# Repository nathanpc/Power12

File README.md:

# Power12

A compact 6 watts per channel amplifier.

## Schematic

It's a very simple discrete power amplifier with a [CFP output stage](http://en.wikipedia.org/wiki/Sziklai_pair).

## Distortion

*Rev A*

Here's the THD x Frequency plot created using [plot_thd.py](https://gist.github.com/nathanpc/464b65f48d494179be13):

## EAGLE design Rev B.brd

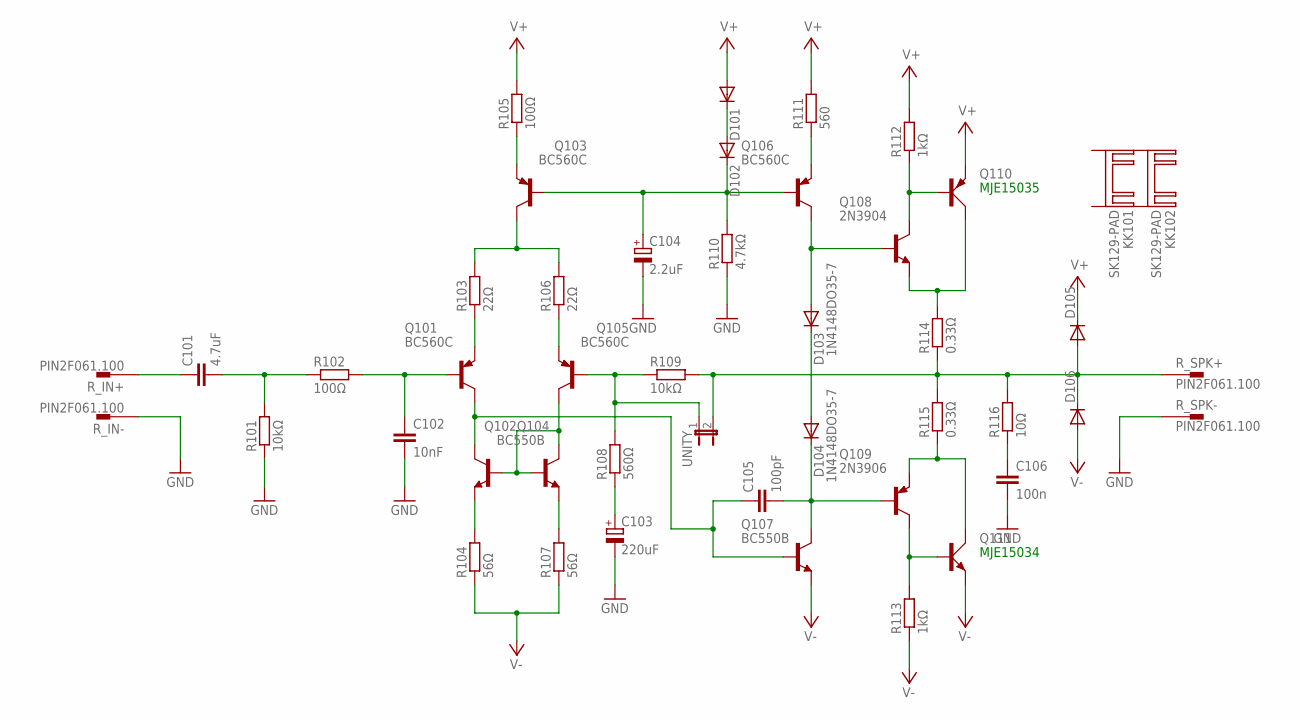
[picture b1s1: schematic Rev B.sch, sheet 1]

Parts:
C101: 4.7uF; C225-113X268
C102: 10nF; C025-025X050
C103: 220uF; E3,5-8
C104: 2.2uF; E2-5
C105: 100pF; C050-050X075
C106: 100n; C075-042X103
D101, D102, D103, D104, D105, D106: 1N4148DO35-7; DO35-7
KK101, KK102: SK129-PAD; SK129
Q101, Q103, Q105, Q106: BC560C; TO92-EBC
Q102, Q104, Q107: BC550B; TO92-EBC
Q108: 2N3904; TO92
Q109: 2N3906; TO92
Q110: TIP42C; TO220AV
Q111: TIP41C; TO220AV
R101, R109: 10kΩ; 0207/10
R102, R105: 100Ω; 0207/10
R103, R106: 22Ω; 0207/10
R104, R107: 56Ω; 0207/10
R108: 560Ω; 0207/10
R110: 4.7kΩ; 0207/10
R111: 560; 0207/10
R112, R113: 1kΩ; 0207/10
R114, R115: 0.33Ω; 0309/12
R116: 10Ω; 0617V
R_IN+: PIN2F061.100; F061.100
R_IN-: PIN2F061.100; F061.100
R_SPK+: PIN2F061.100; F061.100
R_SPK-: PIN2F061.100; F061.100
UNITY: JP1E; JP1

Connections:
GND: C102.2, C103.-, C104.-, C106.2, R101.1, R110.1, R_IN-.A1, R_IN-.A2, R_SPK-.A1, R_SPK-.A2; also elsewhere on the board
unnamed: D103.A, Q106.C, Q108.2 (B)
unnamed: Q105.E, R106.1
unnamed: Q102.B, Q104.B, Q104.C, Q105.C
unnamed: C102.1, Q101.B, R102.2
unnamed: C101.2, R101.2, R102.1
unnamed: C104.+, D102.C, Q103.B, Q106.B, R110.2
unnamed: C101.1, R_IN+.A1, R_IN+.A2
unnamed: C105.1, Q101.C, Q102.C, Q107.B
unnamed: D101.C, D102.A
unnamed: Q106.E, R111.1
unnamed: C103.+, R108.1
unnamed: Q102.E, R104.2
unnamed: Q104.E, R107.2
unnamed: C106.1, R116.1
unnamed: Q101.E, R103.1
unnamed: Q103.C, R103.2, R106.2
unnamed: Q103.E, R105.1
unnamed: D103.C, D104.A
unnamed: Q108.1 (C), Q110.B, R112.1
unnamed: Q109.1 (C), Q111.B, R113.2
unnamed: Q109.3 (E), Q111.C, R115.1
unnamed: Q108.3 (E), Q110.C, R114.2
unnamed: C105.2, D104.C, Q107.C, Q109.2 (B)
unnamed: Q105.B, R108.2, R109.1, UNITY.1
R_OUT: D105.A, D106.C, R109.2, R114.1, R115.2, R116.2, R_SPK+.A1, R_SPK+.A2, UNITY.2
V+: D101.A, D105.C, Q110.E, R105.2, R111.2, R112.2; also elsewhere on the board
V-: D106.A, Q107.E, Q111.E, R104.1, R107.1, R113.1; also elsewhere on the board

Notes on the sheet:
MJE15035
MJE15034

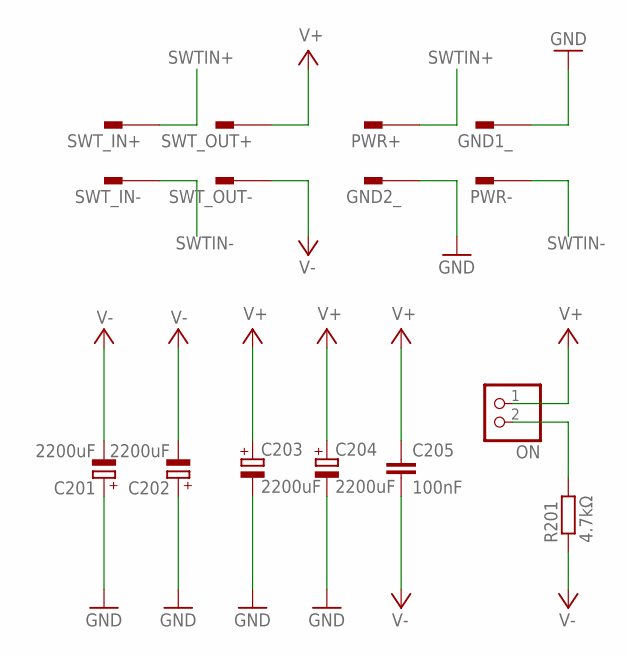
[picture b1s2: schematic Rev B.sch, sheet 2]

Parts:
C201, C202, C203, C204: 2200uF; E5-10,5
C205: 100nF; C025-025X050
GND1_, GND2_: PIN2F061.100; F061.100
ON: JST_2PIN-THM; JST-PH-2-THM
PWR+: PIN2F061.100; F061.100
PWR-: PIN2F061.100; F061.100
R201: 4.7kΩ; 0207/10
SWT_IN+: PIN2F061.100; F061.100
SWT_IN-: PIN2F061.100; F061.100
SWT_OUT+: PIN2F061.100; F061.100
SWT_OUT-: PIN2F061.100; F061.100

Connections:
GND: C201.+, C202.+, C203.-, C204.-, GND1_.A1, GND1_.A2, GND2_.A1, GND2_.A2; also elsewhere on the board
unnamed: ON.2 (1), R201.2
SWTIN+: PWR+.A1, PWR+.A2, SWT_IN+.A1, SWT_IN+.A2
SWTIN-: PWR-.A1, PWR-.A2, SWT_IN-.A1, SWT_IN-.A2
V+: C203.+, C204.+, C205.1, ON.1 (2), SWT_OUT+.A1, SWT_OUT+.A2; also elsewhere on the board
V-: C201.-, C202.-, C205.2, R201.1, SWT_OUT-.A1, SWT_OUT-.A2; also elsewhere on the board

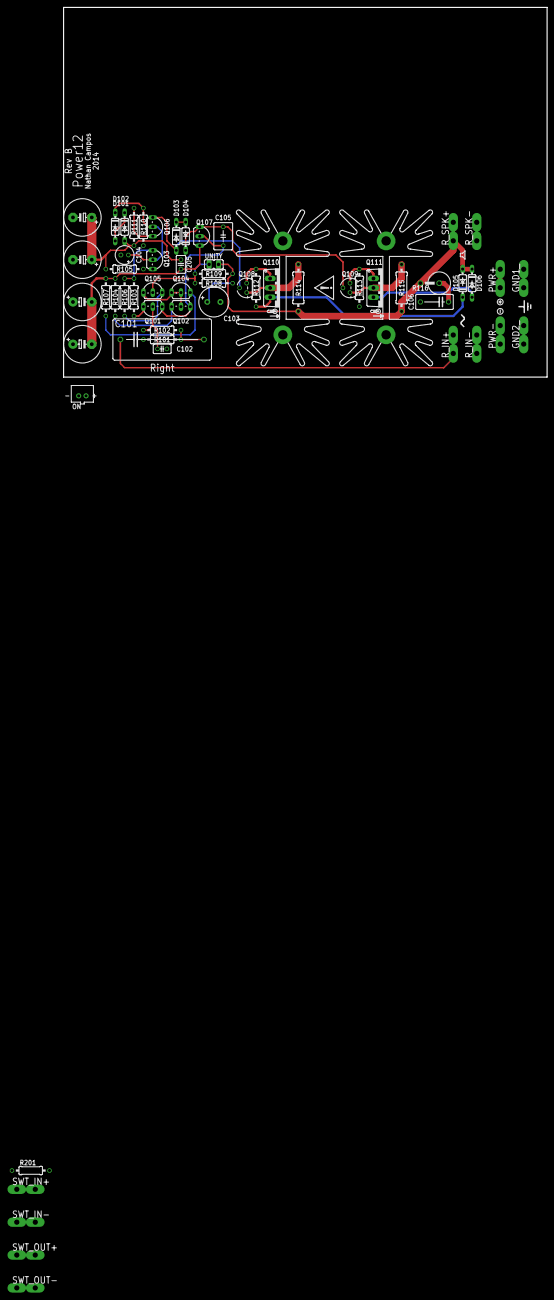
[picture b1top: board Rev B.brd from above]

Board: 4 copper layers, 130.8 x 100.0 mm, 69 parts (0 on the bottom side), 31 nets.

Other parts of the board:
U$1: ICON_SPEAKER
U$2: ICON_GND2
U$3: ICON_PLUS
U$4: ICON_MINUS
U$5, U$6: ICON_TEMP
U$7: ICON_AC
U$9: ICON_EXL-S

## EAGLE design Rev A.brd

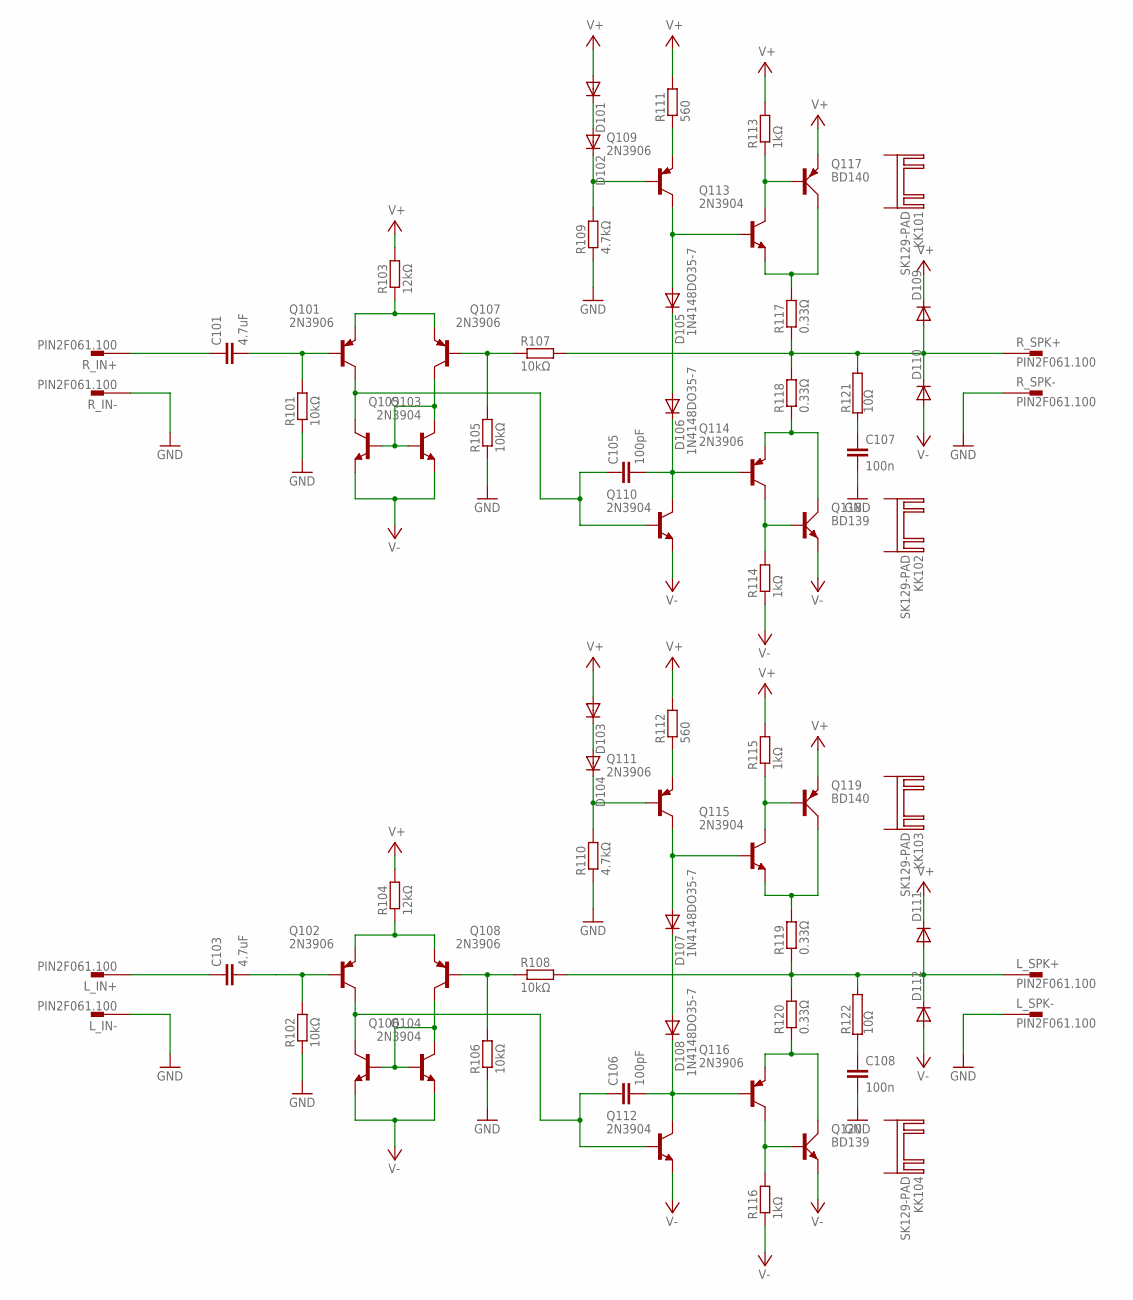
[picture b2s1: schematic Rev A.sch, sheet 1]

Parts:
C101, C103: 4.7uF; C225-113X268
C105, C106: 100pF; C050-050X075
C107, C108: 100n; C075-042X103
D101, D102, D103, D104, D105, D106, D107, D108, D109, D110, D111, D112: 1N4148DO35-7; DO35-7
KK101, KK102, KK103, KK104: SK129-PAD; SK129
L_IN+: PIN2F061.100; F061.100
L_IN-: PIN2F061.100; F061.100
L_SPK+: PIN2F061.100; F061.100
L_SPK-: PIN2F061.100; F061.100
Q101, Q102, Q107, Q108, Q109, Q111, Q114, Q116: 2N3906; TO92
Q103, Q104, Q105, Q106, Q110, Q112, Q113, Q115: 2N3904; TO92
Q117, Q119: BD140; TO126AV
Q118, Q120: BD139; TO126AV
R101, R102, R105, R106, R107, R108: 10kΩ; 0207/10
R103, R104: 12kΩ; 0207/10
R109, R110: 4.7kΩ; 0207/10
R111, R112: 560; 0207/10
R113, R114, R115, R116: 1kΩ; 0207/10
R117, R118, R119, R120: 0.33Ω; 0309/12
R121, R122: 10Ω; MNS-5
R_IN+: PIN2F061.100; F061.100
R_IN-: PIN2F061.100; F061.100
R_SPK+: PIN2F061.100; F061.100
R_SPK-: PIN2F061.100; F061.100

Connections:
GND: C107.2, C108.2, L_IN-.A1, L_IN-.A2, L_SPK-.A1, L_SPK-.A2, R101.1, R102.1, R105.1, R106.1, R109.1, R110.1, R_IN-.A1, R_IN-.A2, R_SPK-.A1, R_SPK-.A2; also elsewhere on the board
L_OUT: D111.A, D112.C, L_SPK+.A1, L_SPK+.A2, R108.2, R119.1, R120.2, R122.2
unnamed: D105.A, Q109.1 (C), Q113.2 (B)
unnamed: Q101.3 (E), Q107.3 (E), R103.1
unnamed: Q103.2 (B), Q105.1 (C), Q105.2 (B), Q107.1 (C)
unnamed: Q104.2 (B), Q106.1 (C), Q106.2 (B), Q108.1 (C)
unnamed: C101.2, Q101.2 (B), R101.2
unnamed: D102.C, Q109.2 (B), R109.2
unnamed: C101.1, R_IN+.A1, R_IN+.A2
unnamed: C105.1, Q101.1 (C), Q103.1 (C), Q110.2 (B)
unnamed: D101.C, D102.A
unnamed: Q109.3 (E), R111.1
unnamed: D104.C, Q111.2 (B), R110.2
unnamed: D103.C, D104.A
unnamed: Q111.3 (E), R112.1
unnamed: C103.1, L_IN+.A1, L_IN+.A2
unnamed: C107.1, R121.1
unnamed: C108.1, R122.1
unnamed: D105.C, D106.A
unnamed: C103.2, Q102.2 (B), R102.2
unnamed: Q113.1 (C), Q117.B, R113.1
unnamed: Q114.1 (C), Q118.B, R114.2
unnamed: Q114.3 (E), Q118.C, R118.1
unnamed: Q113.3 (E), Q117.C, R117.2
unnamed: C105.2, D106.C, Q110.1 (C), Q114.2 (B)
unnamed: Q107.2 (B), R105.2, R107.1
unnamed: Q102.3 (E), Q108.3 (E), R104.1
unnamed: C106.1, Q102.1 (C), Q104.1 (C), Q112.2 (B)
unnamed: D107.C, D108.A
unnamed: D107.A, Q111.1 (C), Q115.2 (B)
unnamed: Q115.1 (C), Q119.B, R115.1
unnamed: Q115.3 (E), Q119.C, R119.2
unnamed: Q116.1 (C), Q120.B, R116.2
unnamed: Q116.3 (E), Q120.C, R120.1
unnamed: C106.2, D108.C, Q112.1 (C), Q116.2 (B)
unnamed: Q108.2 (B), R106.2, R108.1
R_OUT: D109.A, D110.C, R107.2, R117.1, R118.2, R121.2, R_SPK+.A1, R_SPK+.A2
V+: D101.A, D103.A, D109.C, D111.C, Q117.E, Q119.E, R103.2, R104.2, R111.2, R112.2, R113.2, R115.2; also elsewhere on the board
V-: D110.A, D112.A, Q103.3 (E), Q104.3 (E), Q105.3 (E), Q106.3 (E), Q110.3 (E), Q112.3 (E), Q118.E, Q120.E, R114.1, R116.1; also elsewhere on the board

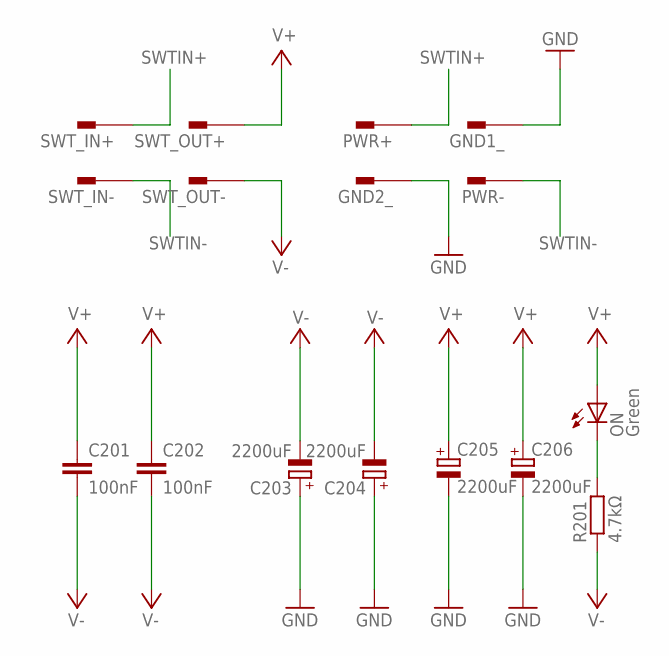
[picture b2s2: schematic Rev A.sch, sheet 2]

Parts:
C201, C202: 100nF; C025-025X050
C203, C204, C205, C206: 2200uF; E5-10,5
GND1_, GND2_: PIN2F061.100; F061.100
ON: Green; LED5MM
PWR+: PIN2F061.100; F061.100
PWR-: PIN2F061.100; F061.100
R201: 4.7kΩ; 0207/10
SWT_IN+: PIN2F061.100; F061.100
SWT_IN-: PIN2F061.100; F061.100
SWT_OUT+: PIN2F061.100; F061.100
SWT_OUT-: PIN2F061.100; F061.100

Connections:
GND: C203.+, C204.+, C205.-, C206.-, GND1_.A1, GND1_.A2, GND2_.A1, GND2_.A2; also elsewhere on the board
unnamed: ON.K (C), R201.2
SWTIN+: PWR+.A1, PWR+.A2, SWT_IN+.A1, SWT_IN+.A2
SWTIN-: PWR-.A1, PWR-.A2, SWT_IN-.A1, SWT_IN-.A2
V+: C201.1, C202.1, C205.+, C206.+, ON.A, SWT_OUT+.A1, SWT_OUT+.A2; also elsewhere on the board
V-: C201.2, C202.2, C203.-, C204.-, R201.1, SWT_OUT-.A1, SWT_OUT-.A2; also elsewhere on the board

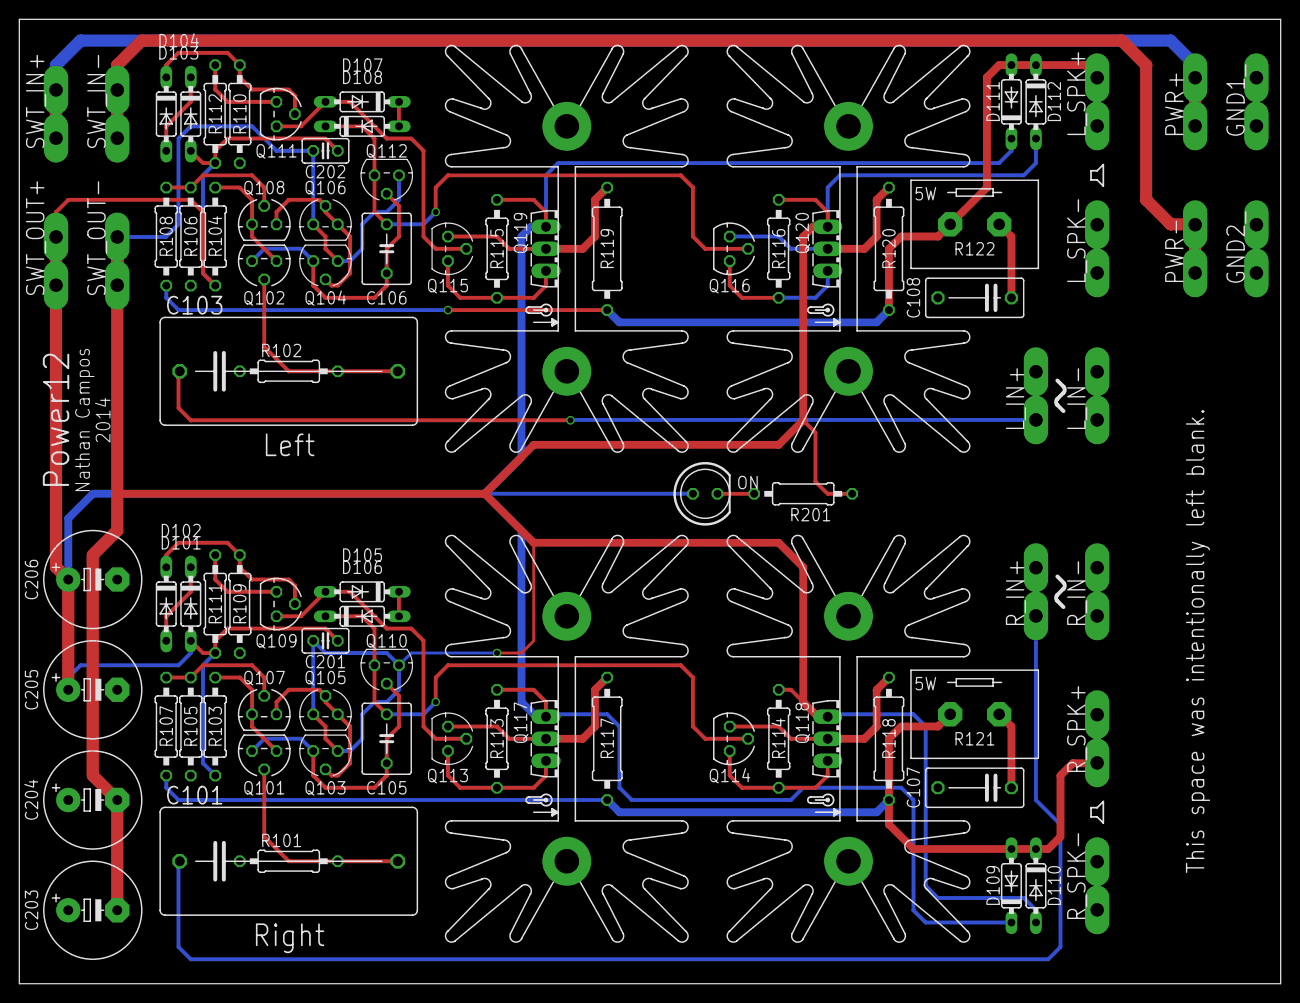
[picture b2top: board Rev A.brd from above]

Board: 4 copper layers, 130.8 x 100.0 mm, 96 parts (0 on the bottom side), 42 nets.

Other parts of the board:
U$1, U$2: ICON_SPEAKER
U$3, U$4, U$5, U$6: ICON_TEMP
U$7, U$8: ICON_AC

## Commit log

2014-09-13 Final schematic?
2014-09-13 Switched every JST connector to a Faston tab
2014-09-13 Components placed
2014-09-14 Finished the board layout
2014-09-14 Exported the schematic
2014-09-14 Ready for production
2014-09-14 Updated the README
2014-10-12 Updated the README with a picture of the real thing
2014-10-12 Temperature profile
2014-10-12 Added the SPICE circuit and the THD plot
2014-10-12 Create gh-pages branch via GitHub
2014-10-12 Added the temperature profile plot
2014-10-25 Started working on Rev B
2014-10-26 Finished routing one side
2014-10-26 Rev B

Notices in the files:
parts and their libraries:
dicons: Copyright (C) 2004, Bob Starr (rtzaudio@mindspring.com)
